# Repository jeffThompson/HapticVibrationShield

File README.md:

Haptic Vibration Shield
=====================

Haptic vibration shield for Arduino: 4 vibration motors and the [TI DRV2603 haptic driver IC](http://www.ti.com/product/drv2603).

Above preview from boards ordered from [OSH Park](http://oshpark.com/) (a great way to get some if you want them). Created with generous assistance from Harvestworks' Cultural Innovation Fund program.

Note: the layout for the DRV2603 is (not quite yet) guaranteed. Please stay tuned!

\- \- \-

\[ all resources available under [Creative Commons BY-NC-SA license](http://creativecommons.org/licenses/by-nc-sa/3.0/) - feel free to use but [please let me know](http://www.jeffreythompson.org) \]

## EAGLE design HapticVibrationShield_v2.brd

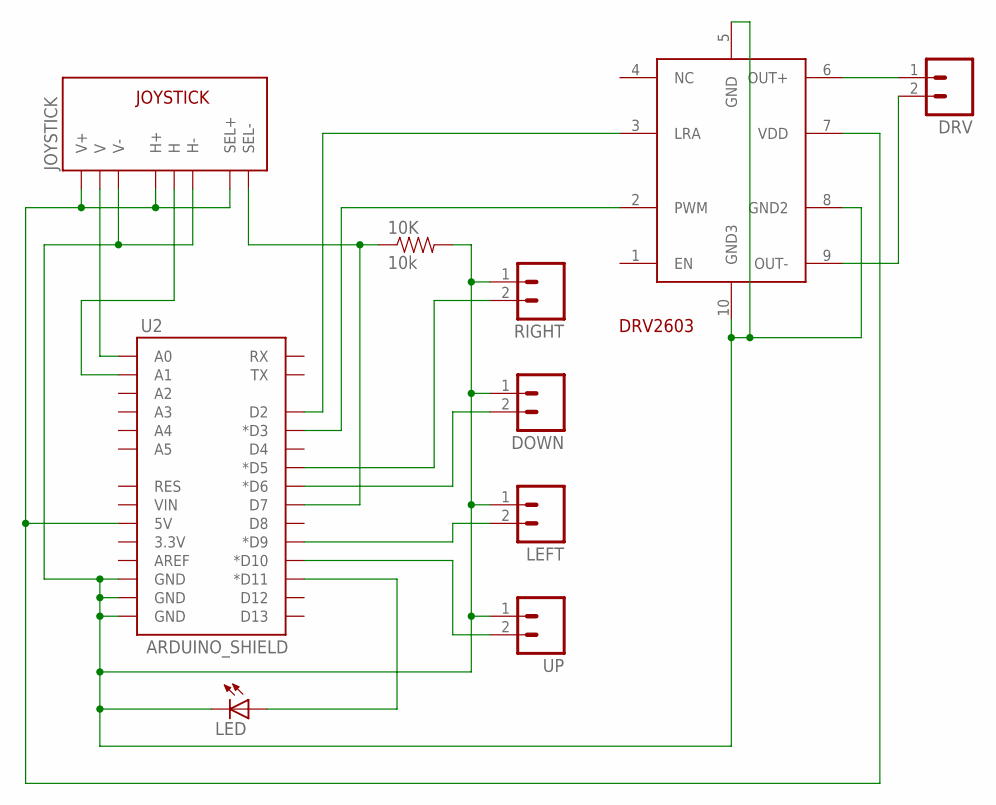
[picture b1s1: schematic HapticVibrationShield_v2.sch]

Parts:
10K: 10k; R2010
DOWN: M02LOCK_LONGPADS; 1X02_LOCK_LONGPADS
DRV: M02LOCK_LONGPADS; 1X02_LOCK_LONGPADS
DRV2603: QFN-10QFN-10; QFN-10
JOYSTICK: JOYSTICKPTH; JOYSTICK
LED: LED5MM
LEFT: M02LOCK_LONGPADS; 1X02_LOCK_LONGPADS
RIGHT: M02LOCK_LONGPADS; 1X02_LOCK_LONGPADS
U2: ARDUINO_SHIELD; DUEMILANOVE_SHIELD
UP: M02LOCK_LONGPADS; 1X02_LOCK_LONGPADS

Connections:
GND: 10K.2, DOWN.1, DRV2603.5 (GND), DRV2603.8 (GND2), DRV2603.10 (GND3), JOYSTICK.H3 (H-), JOYSTICK.V3 (V-), LED.K (C), LEFT.1, RIGHT.1, U2.GND@0 (GND), U2.GND@1 (GND), U2.GND@2 (GND), UP.1
unnamed: DOWN.2, U2.D6 (*D6)
unnamed: LEFT.2, U2.D9 (*D9)
unnamed: RIGHT.2, U2.D5 (*D5)
unnamed: U2.D10 (*D10), UP.2
unnamed: DRV2603.7 (VDD), JOYSTICK.B1A (SEL+), JOYSTICK.H1 (H+), JOYSTICK.V1 (V+), U2.5V
unnamed: JOYSTICK.V2 (V), U2.A0
unnamed: JOYSTICK.H2 (H), U2.A1
unnamed: 10K.1, JOYSTICK.B2A (SEL-), U2.D7
unnamed: LED.A, U2.D11 (*D11)
unnamed: DRV.1, DRV2603.6 (OUT+)
unnamed: DRV.2, DRV2603.9 (OUT-)
unnamed: DRV2603.2 (PWM), U2.D3 (*D3)
unnamed: DRV2603.3 (LRA), U2.D2

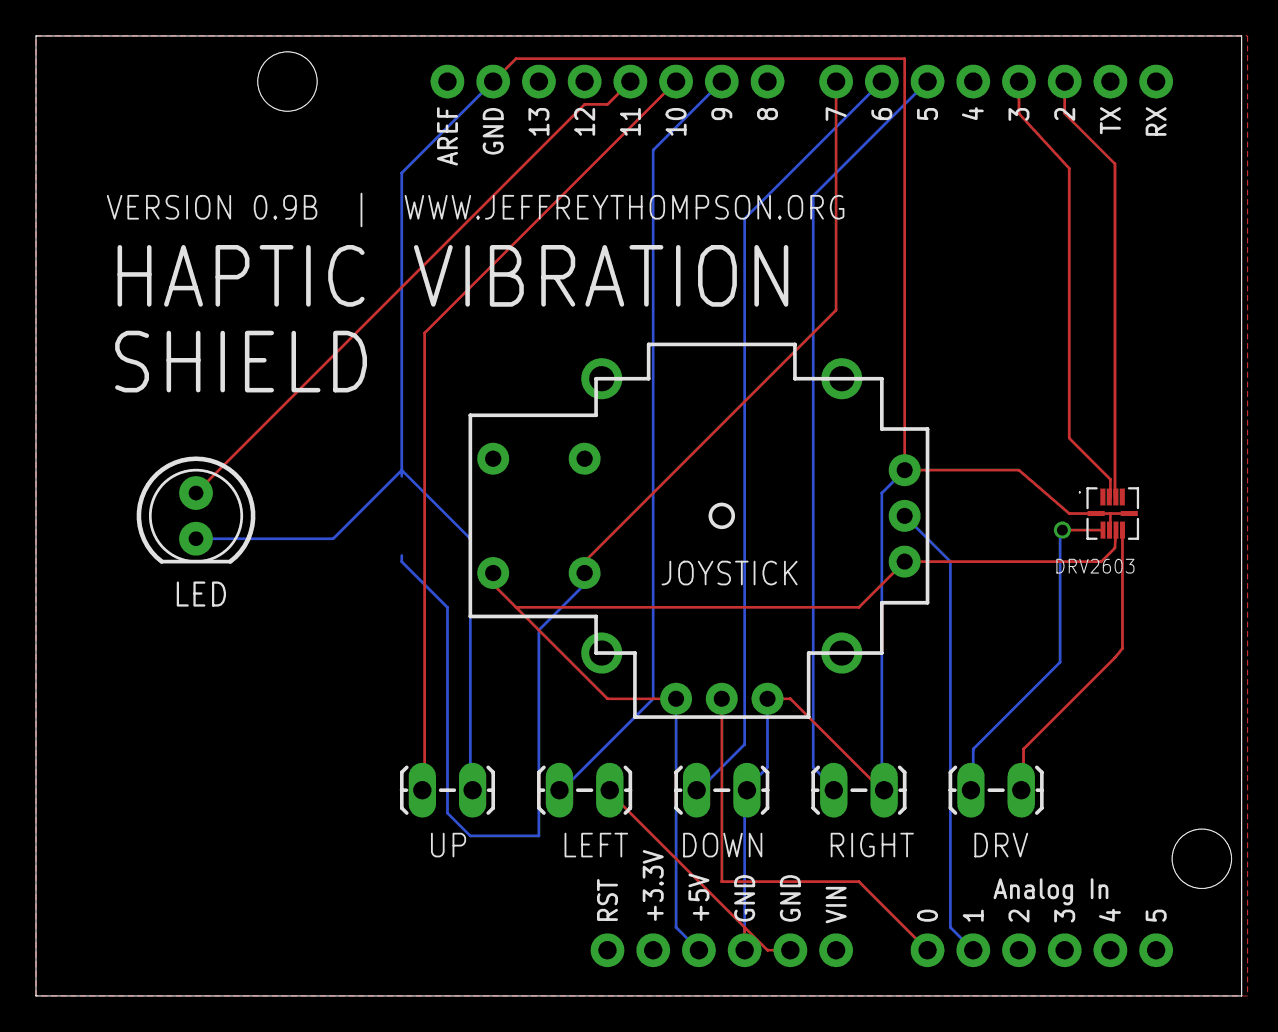
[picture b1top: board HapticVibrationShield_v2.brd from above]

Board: 2 copper layers, 67.0 x 53.3 mm, 10 parts (1 on the bottom side), 14 nets.

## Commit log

2013-07-14 Updated PCB, added datasheet for DRV2603
2013-10-06 Updated PCB image

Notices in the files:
parts and their libraries:
SparkFun-Boards: Licensing: CC v3.0 Share-Alike You are welcome to use this library for commercial purposes.
